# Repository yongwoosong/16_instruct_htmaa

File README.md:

# 16_instruct_htmaa
Fab Academy 2016 _ instructing guide archive

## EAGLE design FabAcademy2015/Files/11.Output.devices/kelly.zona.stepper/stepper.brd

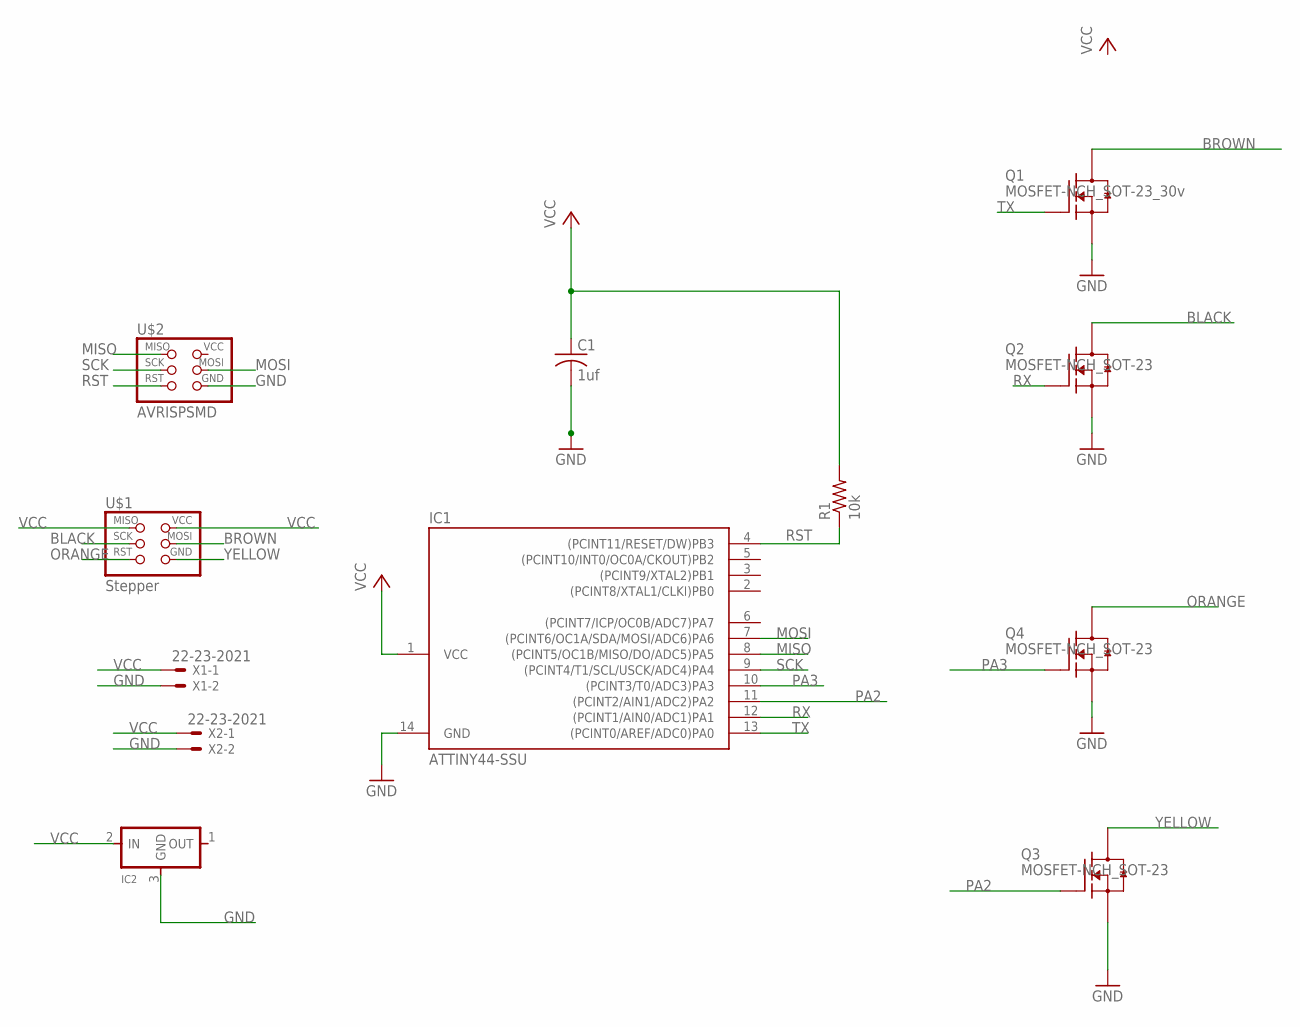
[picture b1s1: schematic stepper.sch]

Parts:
C1: 1uf; C1206
IC1: ATTINY44-SSU; SOIC14
IC2: REGULATORSOT23; SOT23
Q1: MOSFET-NCH_SOT-23_30v; SOT95P280X135-3N
Q2, Q3, Q4: MOSFET-NCH_SOT-23; SOT95P280X135-3N
R1: 10k; R1206
U$1: Stepper; 2X03SMD
U$2: AVRISPSMD; 2X03SMD
X1, X2: 22-23-2021

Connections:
BLACK: Q2.3 (D), U$1.3 (SCK)
BROWN: Q1.3 (D), U$1.4 (MOSI)
GND: C1.2, IC1.14 (GND), IC2.3 (GND), Q1.2 (S), Q2.2 (S), Q3.2 (S), Q4.2 (S), U$2.6 (GND), X1.2, X2.2
MISO: IC1.8 ((PCINT5/OC1B/MISO/DO/ADC5)PA5), U$2.1 (MISO)
MOSI: IC1.7 ((PCINT6/OC1A/SDA/MOSI/ADC6)PA6), U$2.4 (MOSI)
ORANGE: Q4.3 (D), U$1.5 (RST)
OUT: C1.1, R1.2
PA2: IC1.11 ((PCINT2/AIN1/ADC2)PA2), Q3.1 (G)
PA3: IC1.10 ((PCINT3/T0/ADC3)PA3), Q4.1 (G)
RST: IC1.4 ((PCINT11/RESET/DW)PB3), R1.1, U$2.5 (RST)
RX: IC1.12 ((PCINT1/AIN0/ADC1)PA1), Q2.1 (G)
SCK: IC1.9 ((PCINT4/T1/SCL/USCK/ADC4)PA4), U$2.3 (SCK)
TX: IC1.13 ((PCINT0/AREF/ADC0)PA0), Q1.1 (G)
VCC: IC1.1 (VCC), IC2.2 (IN), U$1.1 (MISO), U$1.2 (VCC), X1.1, X2.1
YELLOW: Q3.3 (D), U$1.6 (GND)

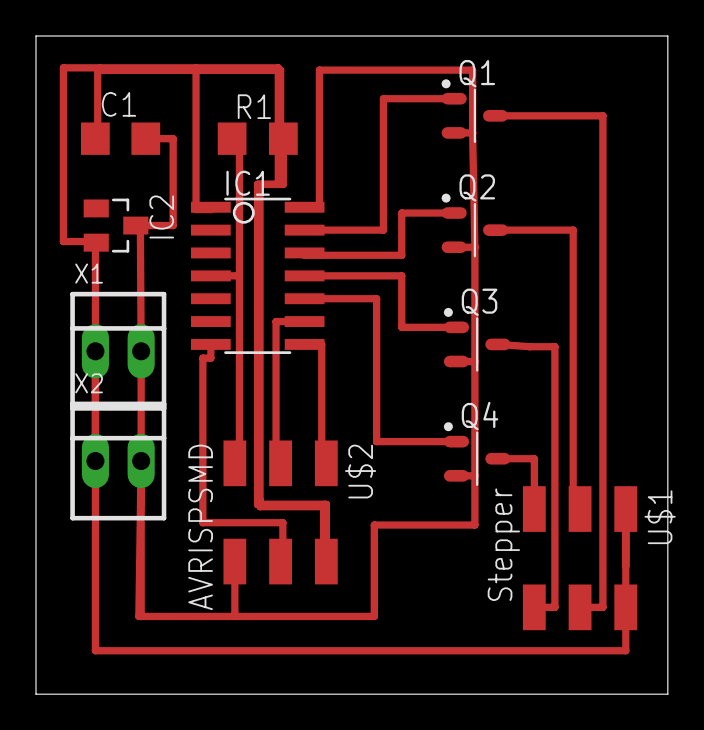
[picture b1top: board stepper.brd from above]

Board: 2 copper layers, 35.1 x 36.6 mm, 12 parts (0 on the bottom side), 15 nets.

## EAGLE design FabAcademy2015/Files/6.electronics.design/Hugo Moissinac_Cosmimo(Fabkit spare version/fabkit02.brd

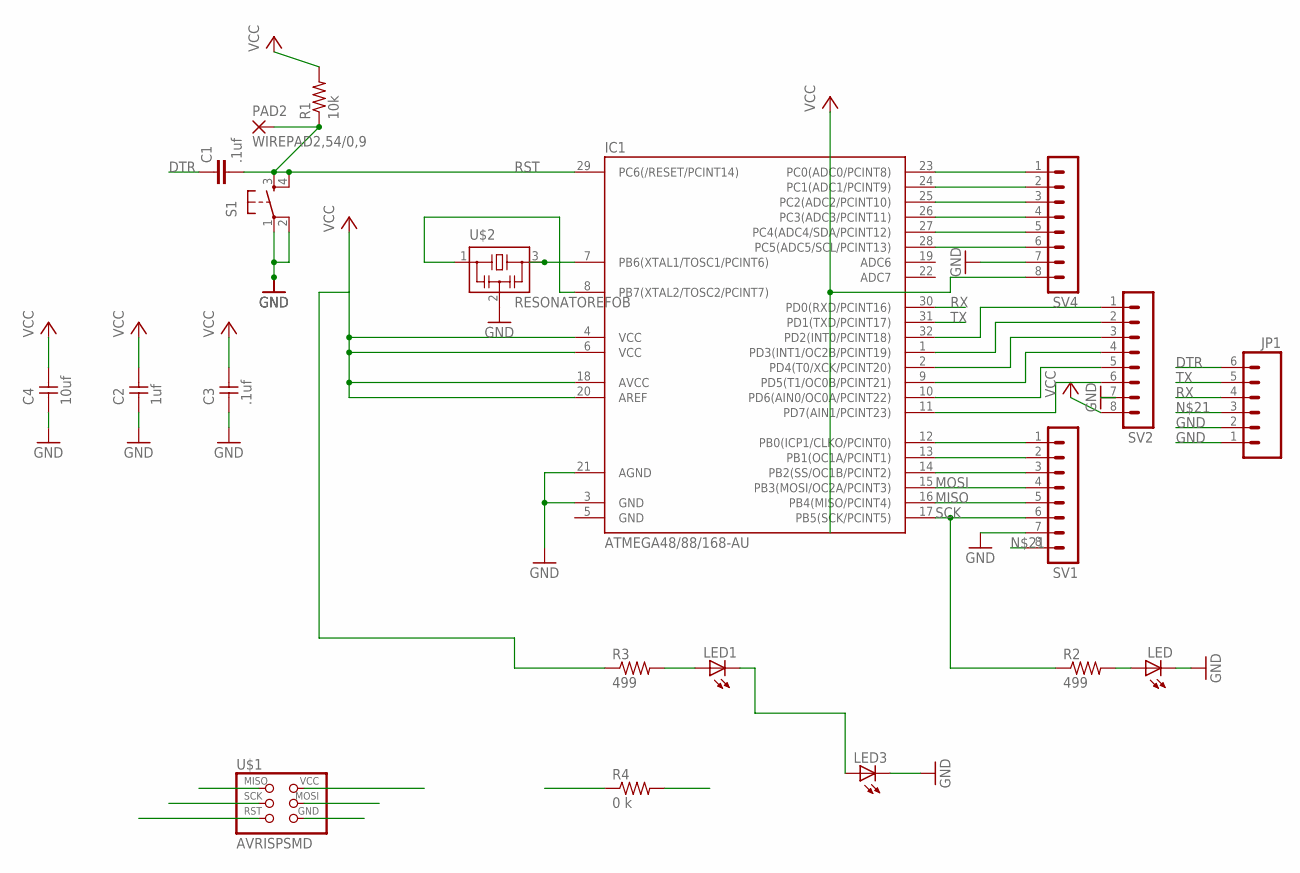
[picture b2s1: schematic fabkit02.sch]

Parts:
C1: .1uf; C1206
C2: 1uf; 1206
C3: .1uf; 1206
C4: 10uf; 1206
IC1: ATMEGA48/88/168-AU; TQFP32-08
JP1: M06SMD; 1X06-SMD
LED, LED1, LED3: LED1206; 1206
PAD2: WIREPAD2,54/0,9; 2,54/0,9
R1: 10k; 1206
R2, R3: 499; 1206
R4: 0 k; 1206
S1: 6MM_SWITCH6MM_SWITCH; 6MM_SWITCH
SV1, SV2, SV4: MA08-1
U$1: AVRISPSMD; 2X03SMD
U$2: RESONATOREFOB; EFOBM

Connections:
DTR: C1.1, JP1.6
GND: C2.1, C3.1, C4.1, IC1.3 (GND), IC1.5 (GND), IC1.21 (AGND), JP1.1, JP1.2, LED.2 (C), LED3.2 (C), S1.1, S1.2 (P1), SV1.7, SV2.7, SV4.7, U$1.6 (GND), U$2.2
MISO: IC1.16 (PB4(MISO/PCINT4)), SV1.5, U$1.1 (MISO)
MOSI: IC1.15 (PB3(MOSI/OC2A/PCINT3)), R4.1, R4.2, SV1.4, U$1.4 (MOSI)
unnamed: IC1.8 (PB7(XTAL2/TOSC2/PCINT7)), U$2.1
unnamed: IC1.12 (PB0(ICP1/CLKO/PCINT0)), SV1.1
unnamed: IC1.23 (PC0(ADC0/PCINT8)), SV4.1
unnamed: IC1.24 (PC1(ADC1/PCINT9)), SV4.2
unnamed: IC1.25 (PC2(ADC2/PCINT10)), SV4.3
unnamed: IC1.26 (PC3(ADC3/PCINT11)), SV4.4
unnamed: IC1.27 (PC4(ADC4/SDA/PCINT12)), SV4.5
unnamed: IC1.28 (PC5(ADC5/SCL/PCINT13)), SV4.6
unnamed: IC1.7 (PB6(XTAL1/TOSC1/PCINT6)), U$2.3
unnamed: IC1.32 (PD2(INT0/PCINT18)), SV2.1
unnamed: IC1.1 (PD3(INT1/OC2B/PCINT19)), SV2.2
unnamed: IC1.2 (PD4(T0/XCK/PCINT20)), SV2.3
unnamed: IC1.9 (PD5(T1/OC0B/PCINT21)), SV2.4
unnamed: IC1.10 (PD6(AIN0/OC0A/PCINT22)), SV2.5
unnamed: IC1.11 (PD7(AIN1/PCINT23)), SV2.6
unnamed: LED1.1 (A), R3.2
unnamed: IC1.13 (PB1(OC1A/PCINT1)), SV1.2
unnamed: IC1.14 (PB2(SS/OC1B/PCINT2)), SV1.3
unnamed: LED1.2 (C), LED3.1 (A)
unnamed: C2.2, C3.2, C4.2, IC1.4 (VCC), IC1.6 (VCC), IC1.18 (AVCC), IC1.20 (AREF), JP1.3, R1.2, R3.1, SV1.8, SV2.8, SV4.8, U$1.2 (VCC)
unnamed: LED.1 (A), R2.2
RST: C1.2, IC1.29 (PC6(/RESET/PCINT14)), PAD2.1, R1.1, S1.3 (S), S1.4 (S1), U$1.5 (RST)
RX: IC1.30 (PD0(RXD/PCINT16)), JP1.4
SCK: IC1.17 (PB5(SCK/PCINT5)), R2.1, SV1.6, U$1.3 (SCK)
TX: IC1.31 (PD1(TXD/PCINT17)), JP1.5

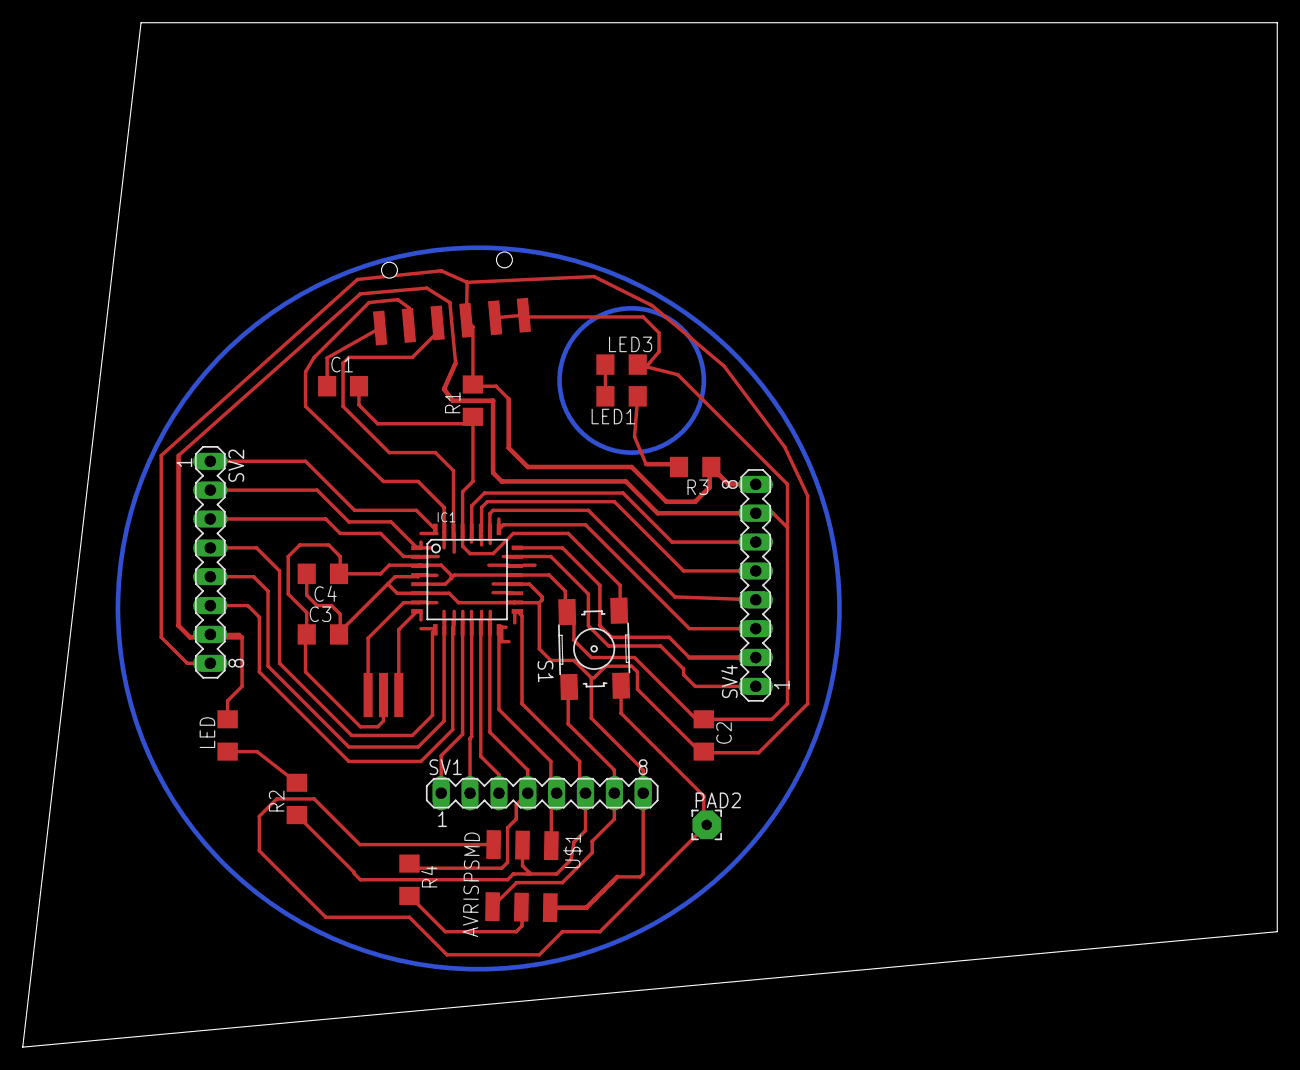
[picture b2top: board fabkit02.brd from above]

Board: 2 copper layers, 110.4 x 90.2 mm, 20 parts (0 on the bottom side), 29 nets.

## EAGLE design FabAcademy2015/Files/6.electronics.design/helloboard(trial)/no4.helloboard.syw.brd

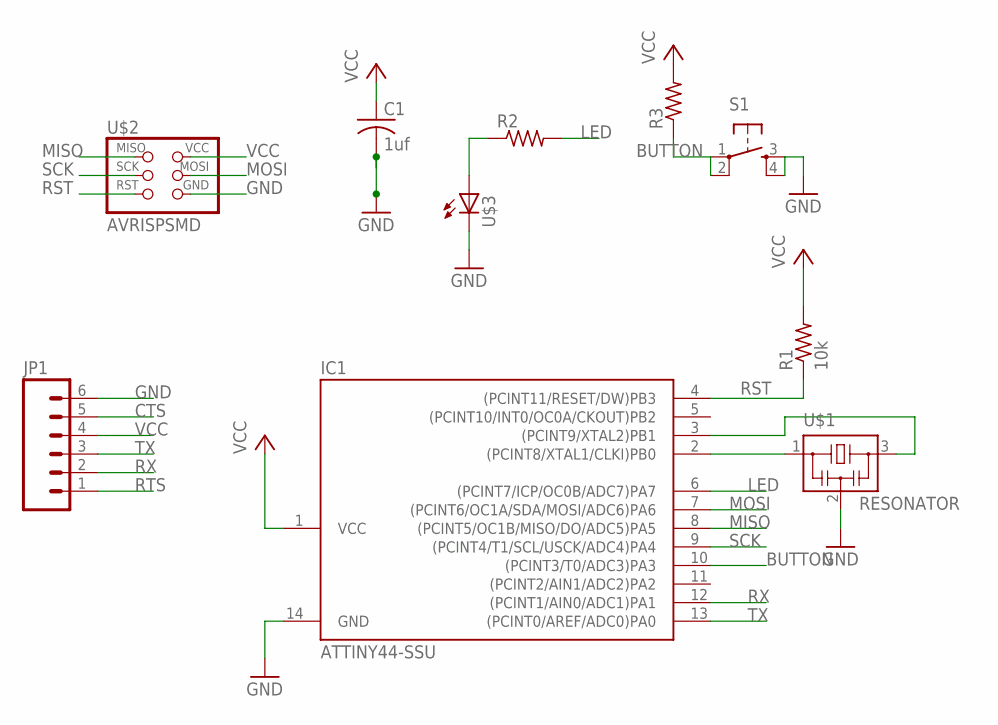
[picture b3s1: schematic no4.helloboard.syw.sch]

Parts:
C1: 1uf; C1206
IC1: ATTINY44-SSU; SOIC14
JP1: M06SMD; 1X06-SMD
R1: 10k; R1206
R2, R3: RESISTOR1206; 1206
S1: 6MM_SWITCH6MM_SWITCH; 6MM_SWITCH
U$1: RESONATOR; EFOBM
U$2: AVRISPSMD; 2X03SMD
U$3: LED1206; 1206

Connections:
BUTTON: IC1.10 ((PCINT3/T0/ADC3)PA3), R3.1, S1.1, S1.2 (P1)
CTS: JP1.5
GND: C1.2, IC1.14 (GND), JP1.6, S1.3 (S), S1.4 (S1), U$1.2, U$2.6 (GND), U$3.2 (C)
LED: IC1.6 ((PCINT7/ICP/OC0B/ADC7)PA7), R2.2
MISO: IC1.8 ((PCINT5/OC1B/MISO/DO/ADC5)PA5), U$2.1 (MISO)
MOSI: IC1.7 ((PCINT6/OC1A/SDA/MOSI/ADC6)PA6), U$2.4 (MOSI)
unnamed: IC1.2 ((PCINT8/XTAL1/CLKI)PB0), U$1.1
unnamed: IC1.3 ((PCINT9/XTAL2)PB1), U$1.3
unnamed: R2.1, U$3.1 (A)
RST: IC1.4 ((PCINT11/RESET/DW)PB3), R1.1, U$2.5 (RST)
RTS: JP1.1
RX: IC1.12 ((PCINT1/AIN0/ADC1)PA1), JP1.2
SCK: IC1.9 ((PCINT4/T1/SCL/USCK/ADC4)PA4), U$2.3 (SCK)
TX: IC1.13 ((PCINT0/AREF/ADC0)PA0), JP1.3
VCC: C1.1, IC1.1 (VCC), JP1.4, R1.2, R3.2, U$2.2 (VCC)

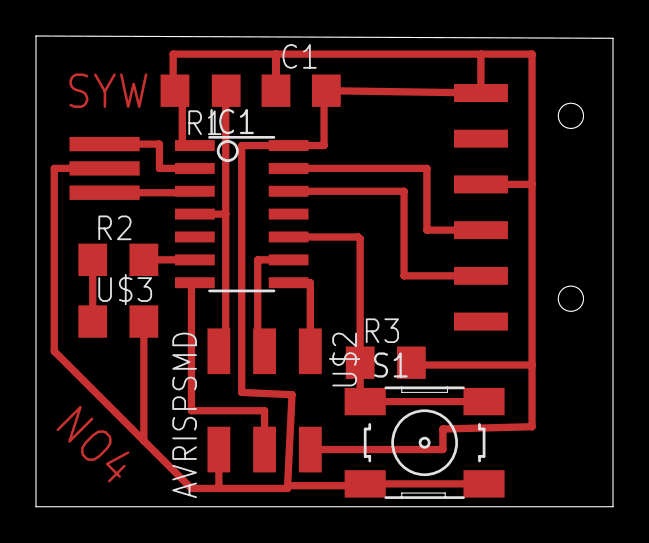
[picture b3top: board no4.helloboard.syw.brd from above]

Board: 1 copper layer, 32.1 x 26.2 mm, 10 parts (0 on the bottom side), 13 nets.

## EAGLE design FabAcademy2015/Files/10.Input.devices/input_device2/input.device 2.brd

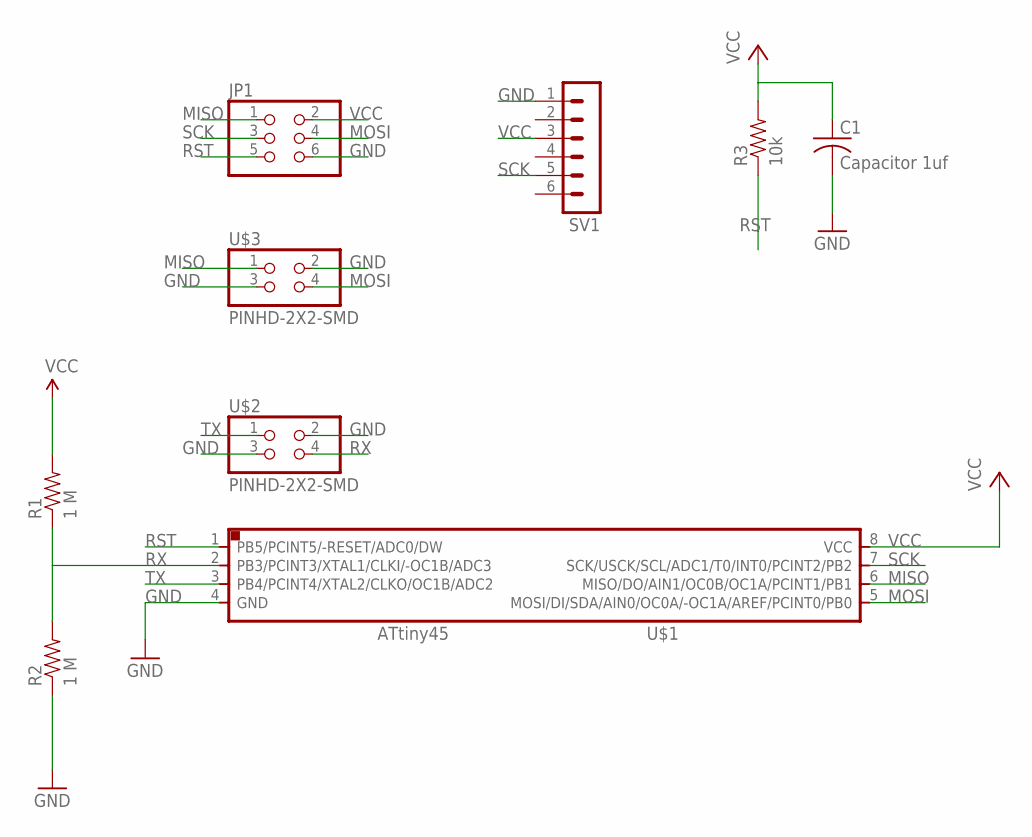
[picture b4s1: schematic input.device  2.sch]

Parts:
C1: Capacitor 1uf; C1206
JP1: PINHD-2X3-SMD; 2X03SMD
R1, R2: 1 M; 1206
R3: 10k; 1206
SV1: MA06-1
U$1: ATTINY45SI; SOIC8
U$2, U$3: PINHD-2X2-SMD; 2X02SMD

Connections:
GND: C1.2, JP1.6, R2.1, SV1.1, U$1.4 (GND), U$2.2, U$2.3, U$3.2, U$3.3
MISO: JP1.1, U$1.6 (MISO/DO/AIN1/OC0B/OC1A/PCINT1/PB1), U$3.1
MOSI: JP1.4, U$1.5 (MOSI/DI/SDA/AIN0/OC0A/-OC1A/AREF/PCINT0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), U$3.4
RST: JP1.5, R3.1, U$1.1 (PB5/PCINT5/-RESET/ADC0/DW)
RX: R1.1, R2.2, U$1.2 (PB3/PCINT3/XTAL1/CLKI/-OC1B/ADC3), U$2.4
SCK: JP1.3, SV1.5, U$1.7 (SCK/USCK/SCL/ADC1/T0/INT0/PCINT2/PB2)
TX: U$1.3 (PB4/PCINT4/XTAL2/CLKO/OC1B/ADC2), U$2.1
VCC: C1.1, JP1.2, R1.2, R3.2, SV1.3, U$1.8 (VCC)

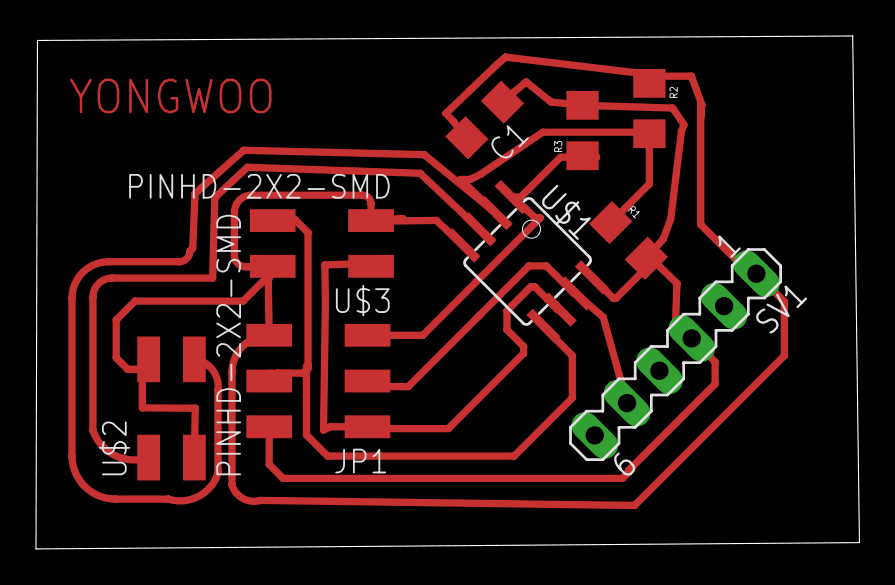
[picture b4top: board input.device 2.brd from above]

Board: 2 copper layers, 45.7 x 28.5 mm, 9 parts (0 on the bottom side), 8 nets.

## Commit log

2016-08-25 document initial upload
2016-08-25 merging the archive
2018-02-19 references.md
2018-02-20 atom references added.
2018-03-02 adding opensource guide
2018-03-22 embedded programming referenced added
2018-04-18 output devices referenced add

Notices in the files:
parts and their libraries:
01_SparkFun: Licensing: CC v3.0 Share-Alike You are welcome to use this library for commercial purposes.
